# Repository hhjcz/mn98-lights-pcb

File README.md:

# MN98 Lights PCB

Passive body-light distribution boards for the MN98 RC car and DumboRC P6DC
receiver. The P6DC already controls the LEDs, so variants in this repository
must not add transistors, MOSFETs, resistors, regulators, capacitors, or GND.

## Shared P6DC Interface

The receiver manual is in `docs/`. The light channels follow the P6DC physical
output order: left cornering, right cornering, brake, flash, back-up, and
daytime running light. Any detachable body-to-chassis cable must preserve that
order without crossed conductors.

Before connecting a body harness, confirm LED polarity with a meter. Do not
infer it from wire colours or connector orientation.

## Archived JST-PH Variant

`v1.0-jst-ph/` contains the original JST-PH work-in-progress, including its
KiCad project, Gerbers, PDFs, connector-specific documentation and skill.
It is preserved as a reference and must not be overwritten by the next design.

## Dupont Body Distributor

`pcb-svetla-mn98.kicad_sch` and `pcb-svetla-mn98.kicad_pcb` are the first
compact passive body-side distributor. The current placement candidate is
32 x 36 mm, within the verified 40 x 50 mm maximum envelope. It uses two
merged right-angle 2.54 mm male headers for paired Dupont LEDs. The left header
contains LEFT TURN and DRL. The right header contains RIGHT TURN, BRAKE,
BACK-UP, MARKER, RAMP and SPARE. Both JST-PH body-link connectors exit left so
their harnesses run toward the same chassis location.
All connector courtyards are inside the board outline. Routing is intentionally
deferred until the mechanical placement and JST-PH orientation are approved.
The JST-PH courtyards are inset 2.5 mm from the left edge to protect the
connectors and leave board material around their through-hole pads.

| Header | Physical pairs, top to bottom |
| --- | --- |
| J1, 1x4 | `COMMON+ / LEFT`, `COMMON+ / DRL` |
| J2, 1x12 | `COMMON+ / RIGHT`, `COMMON+ / BRAKE`, `COMMON+ / BACK-UP`, `COMMON+ / MARKER`, `COMMON+ / RAMP`, `COMMON+ / SPARE` |

JP1, JP2 and JP3 select `DRL` or `FLASH` respectively for MARKER, RAMP and
SPARE. Fit the shunt across pins 1-2 for DRL, or 2-3 for FLASH. All right-angle
connectors face outward from the board. The headers are intentionally unkeyed:
silkscreen marks the common-positive side of every pair. Confirm the supplied
LED pair polarity before connecting power.

### Body Link

The detachable body link uses two right-angle JST-PH 1x4 THT connectors. Pin 1
is `COMMON+` on both connectors, so swapping cables A and B cannot connect a
signal output to common positive; it only exchanges light functions.

| Connector | Pin 1 | Pin 2 | Pin 3 | Pin 4 |
| --- | --- | --- | --- | --- |
| J14, link A | `COMMON+` | `LEFT` | `RIGHT` | `BRAKE` |
| J15, link B | `COMMON+` | `FLASH` | `BACK-UP` | `DRL` |

Use pin-to-pin female-female harnesses. A practical custom-length harness can
be made from two pre-crimped JST-PH 4-pin pigtails joined wire-for-wire. Verify
continuity and pin order with a meter before connecting the receiver.

### Planned P6DC Adapter

A second passive PCB will plug into the six 2-pin P6DC light outputs through a
2x6 Dupont female socket and expose matching J14/J15 JST-PH connectors. It
will join the P6DC common-positive pins and preserve the pinout above. The
adapter is intentionally deferred until its fit against the receiver has been
measured. Both designs may later share one customer-panel PCB for fabrication.

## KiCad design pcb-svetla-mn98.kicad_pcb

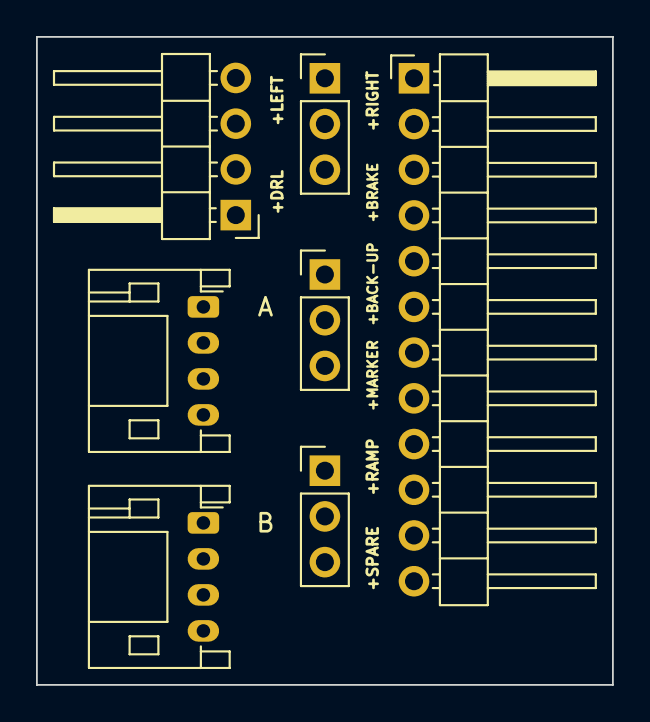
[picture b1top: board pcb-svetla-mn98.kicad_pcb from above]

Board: 2 copper layers, 32.0 x 36.0 mm, 7 parts (0 on the bottom side), 10 nets, no tracks yet.

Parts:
J1: LEFT LIGHT PORTS; PinHeader_1x04_P2.54mm_Horizontal
J2: RIGHT LIGHT PORTS; PinHeader_1x12_P2.54mm_Horizontal
J14: BODY LINK A; JST_PH_S4B-PH-K_1x04_P2.00mm_Horizontal
J15: BODY LINK B; JST_PH_S4B-PH-K_1x04_P2.00mm_Horizontal
JP1: MARKER DRL/FLASH; PinHeader_1x03_P2.54mm_Vertical
JP2: RAMP DRL/FLASH; PinHeader_1x03_P2.54mm_Vertical
JP3: SPARE DRL/FLASH; PinHeader_1x03_P2.54mm_Vertical

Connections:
BACK-UP: J2.6, J15.3
BRAKE: J2.4, J14.4
COMMON+: J1.2, J1.4, J2.1, J2.3, J2.5, J2.7, J2.9, J2.11, J14.1, J15.1
DRL: J1.1, J15.4, JP1.1, JP2.1, JP3.1
FLASH: J15.2, JP1.3, JP2.3, JP3.3
LEFT: J1.3, J14.2
MARKER: J2.8, JP1.2
RAMP: J2.10, JP2.2
RIGHT: J2.2, J14.3
SPARE: J2.12, JP3.2

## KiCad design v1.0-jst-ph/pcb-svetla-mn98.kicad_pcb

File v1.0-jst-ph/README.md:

# MN98 light distribution PCB

Passive 30 x 40 mm, two-layer FR-4 adapter for the MN98 body lighting and
DumboRC P6DC. The board contains no active components and has no GND net.

## Input J14

J14 is an 8-position right-angle JST-PH connector. Pin 1 is marked on the
footprint. P6DC wiring is:

| Pin | Net |
| --- | --- |
| 1 | COMMON+ |
| 2 | COMMON+ |
| 3 | LEFT |
| 4 | RIGHT |
| 5 | BRAKE |
| 6 | FLASH |
| 7 | BACK-UP |
| 8 | DRL |

Pins 1 and 2 are connected to the same 1.2 mm common-positive spine. LED
connector pad 1 is COMMON+ and pad 2 is the controlled P6DC channel.

Pins 3--8 follow the top-to-bottom order of the P6DC light outputs in the
manual: P6DC [14] left cornering, [15] right cornering, [16] brake, [17]
flash, [18] back-up, and [19] daytime running light. Terminate the chassis
cable as J14 pin-to-pin; do not reverse its conductor order between plugs.

## LED outputs

| Connector | Function | Controlled net |
| --- | --- | --- |
| J1 | Left front turn | LEFT |
| J2 | Right front turn | RIGHT |
| J3 | Left rear turn | LEFT |
| J4 | Right rear turn | RIGHT |
| J5 | Spare | FLASH |
| J6 | Left 5 mm headlight | DRL |
| J7 | Left 3 mm marker | MARKER via JP1 |
| J8 | Left rear red | REAR_RED via JP2 |
| J9 | Roof ramp | RAMP via JP3 |
| J10 | Right 5 mm headlight | DRL |
| J11 | Right 3 mm marker | MARKER via JP1 |
| J12 | Right rear red | REAR_RED via JP2 |
| J13 | Spare | DRL |

All J1--J13 are right-angle JST-PH S2B-PH-K footprints.

## Jumper settings

JP1 and JP3 are 1x03 headers. Fit one 2.54 mm shunt between the centre pin
and the selected outside pin.

| Jumper | Left position | Right position |
| --- | --- | --- |
| JP1 | DRL -> MARKER | MARKER -> FLASH |
| JP3 | DRL -> RAMP | RAMP -> FLASH |

JP2 is a 2x03 header. Fit one vertical 2.54 mm shunt in the column labelled
DRL, BRAKE, or BACK-UP to connect that channel to both rear-red connectors.

## Before manufacturing

1. Check that 30 x 40 mm fits the exact available MN98 body cavity.
2. Check the mating housing and the actual pin-1/polarity of every MN98 LED
   lead. Do not infer it from lead colours or connector orientation.
3. Open `pcb-svetla-mn98.kicad_pcb` in KiCad PCB Editor, run DRC, and resolve
   the two JP2 ratsnest indicators before ordering. The generated Gerbers are
   an inspection aid, not a released fabrication package.

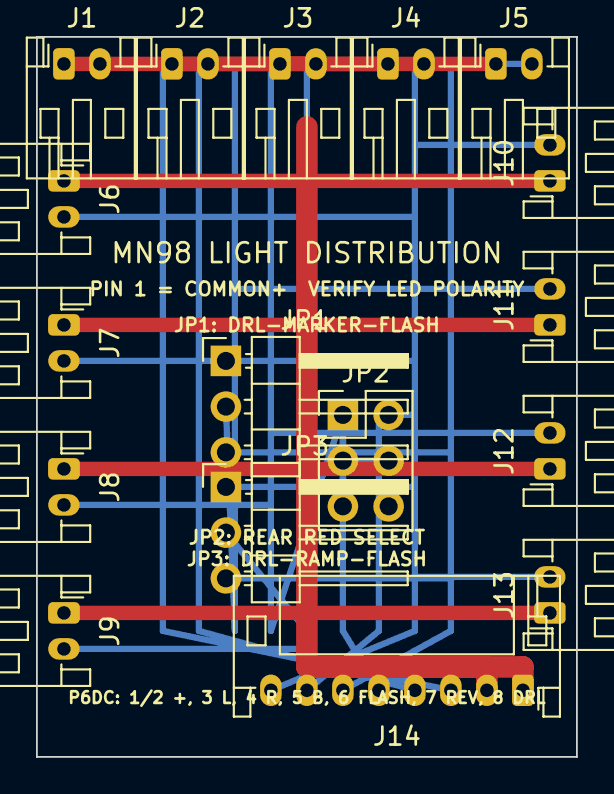
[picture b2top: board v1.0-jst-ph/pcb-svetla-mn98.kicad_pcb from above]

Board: 2 copper layers, 30.0 x 40.0 mm, 17 parts (0 on the bottom side), 10 nets.

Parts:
J1: L TURN FRONT; JST_PH_S2B-PH-K_1x02_P2.00mm_Horizontal
J2: R TURN FRONT; JST_PH_S2B-PH-K_1x02_P2.00mm_Horizontal
J3: L TURN REAR; JST_PH_S2B-PH-K_1x02_P2.00mm_Horizontal
J4: R TURN REAR; JST_PH_S2B-PH-K_1x02_P2.00mm_Horizontal
J5: SPARE FLASH; JST_PH_S2B-PH-K_1x02_P2.00mm_Horizontal
J6: HEADLIGHT L; JST_PH_S2B-PH-K_1x02_P2.00mm_Horizontal
J7: MARKER L; JST_PH_S2B-PH-K_1x02_P2.00mm_Horizontal
J8: REAR RED L; JST_PH_S2B-PH-K_1x02_P2.00mm_Horizontal
J9: ROOF RAMP; JST_PH_S2B-PH-K_1x02_P2.00mm_Horizontal
J10: HEADLIGHT R; JST_PH_S2B-PH-K_1x02_P2.00mm_Horizontal
J11: MARKER R; JST_PH_S2B-PH-K_1x02_P2.00mm_Horizontal
J12: REAR RED R; JST_PH_S2B-PH-K_1x02_P2.00mm_Horizontal
J13: SPARE DRL; JST_PH_S2B-PH-K_1x02_P2.00mm_Horizontal
J14: P6DC INPUT; JST_PH_S8B-PH-K_1x08_P2.00mm_Horizontal
JP1: MARKER: DRL / FLASH; PinHeader_1x03_P2.54mm_Horizontal
JP2: REAR: DRL / BRAKE / BACK-UP; PinHeader_2x03_P2.54mm_Vertical
JP3: RAMP: DRL / FLASH; PinHeader_1x03_P2.54mm_Horizontal

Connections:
/BACK-UP: J14.7, JP2.6
/BRAKE: J14.5, JP2.4
/COMMON+: J1.1, J2.1, J3.1, J4.1, J5.1, J6.1, J7.1, J8.1, J9.1, J10.1, J11.1, J12.1, J13.1, J14.1, J14.2
/DRL: J6.2, J10.2, J13.2, J14.8, JP1.1, JP2.2, JP3.1
/FLASH: J5.2, J14.6, JP1.3, JP3.3
/LEFT: J1.2, J3.2, J14.3
/MARKER: J7.2, J11.2, JP1.2
/RAMP: J9.2, JP3.2
/REAR_RED: J8.2, J12.2, JP2.1, JP2.3, JP2.5
/RIGHT: J2.2, J4.2, J14.4
